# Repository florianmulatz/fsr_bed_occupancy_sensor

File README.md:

# fsr_bed_occupancy_sensor
KiCAD Project for FSR BedOccupancySensor

This is my first try to design a PCB for the FSR - BedOccupancy Sensor from
[Homeassistant Topic](https://community.home-assistant.io/t/fsr-the-best-bed-occupancy-sensor/365795)

Feel free to contribute :)

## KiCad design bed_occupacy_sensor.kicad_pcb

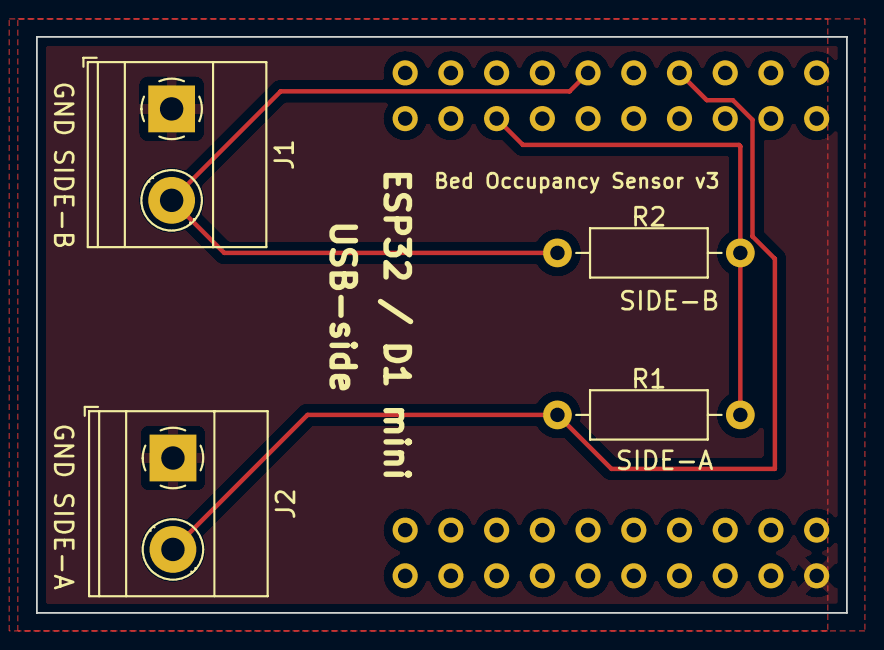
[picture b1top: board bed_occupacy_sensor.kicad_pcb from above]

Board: 2 copper layers, 45.0 x 32.0 mm, 5 parts (0 on the bottom side), 4 nets.

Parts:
J1, J2: Screw_Terminal_01x02; TerminalBlock_Phoenix_MKDS-1,5-2-5.08_1x02_P5.08mm_Horizont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
R1, R2: 1MOhm; R_Axial_DIN0207_L6.3mm_D2.5mm_P10.16mm_Horizontal
U1: mini_esp32; ESP32_mini

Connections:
/SIDE_A: J2.2, R1.2, U1.7 (IO_35)
/SIDE_B: J1.2, R2.2, U1.11 (IO_34)
GND: J1.1, J2.1, U1.22 (GND)
unnamed: R1.1, R2.1, U1.16 (3V3)

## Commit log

2022-12-04 new pcb design all GND connected to ground plane
2022-12-04 Save-Changes again
2022-12-25 pcb update & smaller pcb, groundplate over complete area, drillholes in gerberfiles included
2022-12-25 update in PCB layout / smaller-size, ground-plate over whole PCB
2022-12-25 Update Images in README
2022-12-29 Updated to design ESP32 flipped to get smaller PCB added QR-Code for Project-Link
2022-12-29 deleted old GRB Files from main directory
2022-12-29 removed not needed files
2022-12-30 Update README.md
    Updated pictures
2022-12-30 complete redesign added terminal-block for getting power from external powersupply flipped esp header for getting smaller kicad_pcb added descriptions for pins and QR code
2023-01-12 Reverse the footprint of ESP, as it was the wrong way around
2023-01-13 Updated graphics to relfect KiCAD Project Changes
2023-01-13 fixed design flaw of ESP-Pin orientation (it was the wrong way around). Now the antenna is free (on it's downside) removed QR Code because it's too small to read by a QR-Code-Reader. Updated the resi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
2023-01-13 changed text on silkscreen to v3 reflecting changes in schematic
